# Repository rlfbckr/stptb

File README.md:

# Skills To Pay The Bills!
Online Workshop Series WS2020/21 HfK Bremen

Workshops:

- **2020-11-28** / **10:00** - **18:00** : [Designing Parts for *Machines and Installations* with OpenSCAD](openscad)
- **2020-12-21** / **10:00** - **18:00** : [Designing PCBs with Eagle](eagle)

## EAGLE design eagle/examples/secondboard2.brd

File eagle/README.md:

# Designing PCBs with Eagle

One day introduction into the PCB [(Printed Circuit Board)](https://en.wikipedia.org/wiki/Printed_circuit_board) CAD software **Eagle**  ([www.autodesk.com/products/eagle/overview](hthttps://www.autodesk.com/products/eagle/overview)). The workshop offers a fundamental introduction into concepts, user interface and workflow. A full workflow cycle - form schematic to board layout and the final production in a factory in china - will be explained.

- **Date:** Monday **2020-12-21** / **10:00** - **18:00**
- **Registration:** Send me an email or direct message for a **binding** registration. Please make sure that you are able to join the workshop for the **full day**. (The workshop is limited to **15 participants**)
- The workshop will be held **online via MS Teams.**

## Pre/Requirements:

1. Participants should have **GOOD/SOLID** knowledge in electronics and fundamental electric laws incl. reading schematics, soldering and some experiance with sourcing parts. (At leased you should have already made **some** circuits on breadboards or with perfboard ).
2. It could be helpful to have already a **little** project in mind.
3. Please install the free/educational version of  **EAGLE** form from the [autodesk website](https://www.autodesk.de/products/eagle/free-download?plc=F360&term=1-YEAR&support=ADVANCED&quantity=1). (It's now strangly bundeled with Fursion 360. Look for educational licence )
5. A **three button** mouse incl. **wheel** is **very** helpful!
4. Coffee and food by hand.

## Schedule x Content *(preliminary)*:

* **10:00 - 12:00** | *Fundamentals*

  1. Introduction
     - Why design your own PCBs?
     - Environmental Footprint?
     - *Design*ing PCB as a *designer*?
     - DIP vs SMD?
     - Materials
     - Fabrication in China or at home?
 
  2. Schematics
     - Eagle User Interface and basic concepts.
     - Adding Parts - **KNOW YOU PARTS!!!!!!!!!**
     - Libraries of Parts
     - Connecting Parts
     
  3. Q&A Time I
     - The participants can repeat and experiment the learned and ask questions  
     - Share your screen!

* **12:00 - 13:00** | *Lunch Break*

* **13:00 - 15:00** |  *Layouting a Board*

  4. Placing parts
  5. Ground plate
  6. Routing signals
  7. Vias
  8. Q&A Time II

* **15:00 - 16:00** | *Kaffee x Kuchen Break / BYOC (Bring your own Cake)*

* **16:00 - 18:00** | *Preparing for Production*

  9. Testing and Checking ERC + DRC
  10. Exporting Gerber Files
  11. Uploading files to your chinese manufacturer of choice!

* **18:00** | *EOW*

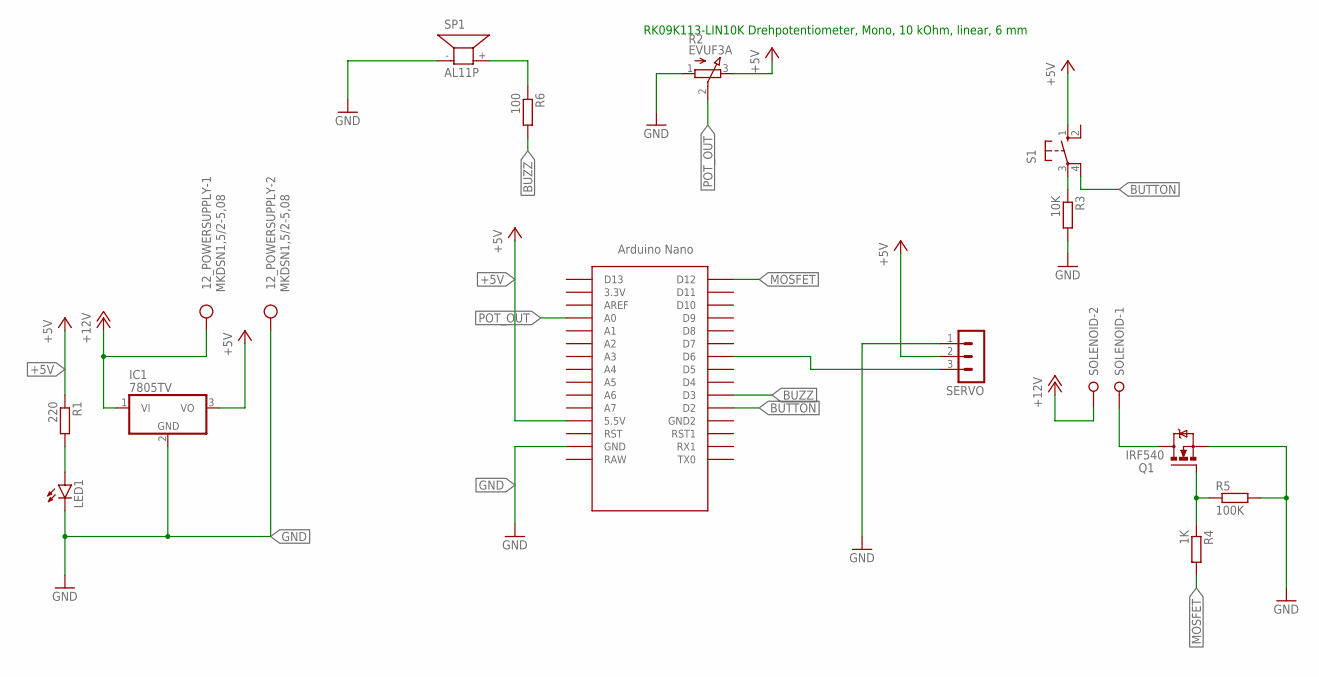
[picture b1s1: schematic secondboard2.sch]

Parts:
12_POWERSUPPLY: MKDSN1,5/2-5,08
IC1: 7805TV; TO220V
LED1: LED3MM
Q1: IRF540; TO220BV
R1: 220; R0805
R2: EVUF3A; EVUF
R3: 10K; R0805
R4: 1K; R0805
R5: 100K; R0805
R6: 100; R0805
S1: 10-XX; B3F-10XX
SERVO: MA03-1
SOLENOID: W237-02P; W237-132
SP1: AL11P
U$1: NANO

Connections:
+5V: IC1.3 (VO), R1.1, R2.3 (E), S1.1 (S), SERVO.2, U$1.5V (5.5V)
+12V: 12_POWERSUPPLY.1, IC1.1 (VI), SOLENOID.2
BUTTON: S1.4 (P1), U$1.D2
BUZZ: R6.2, U$1.D3
CONNECT: LED1.A, R1.2
GND: 12_POWERSUPPLY.2, IC1.2 (GND), LED1.K (C), Q1.S, R2.1 (A), R3.2, R5.2, SERVO.1, SP1.- (1), U$1.GND
MOSFET: R4.2, U$1.D12
unnamed: R3.1, S1.3
unnamed: R6.1, SP1.+ (2)
unnamed: Q1.D, SOLENOID.1
unnamed: SERVO.3, U$1.D6
unnamed: Q1.G, R4.1, R5.1
POT_OUT: R2.2 (S), U$1.A0

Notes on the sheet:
RK09K113-LIN10K Drehpotentiometer, Mono, 10 kOhm, linear, 6 mm

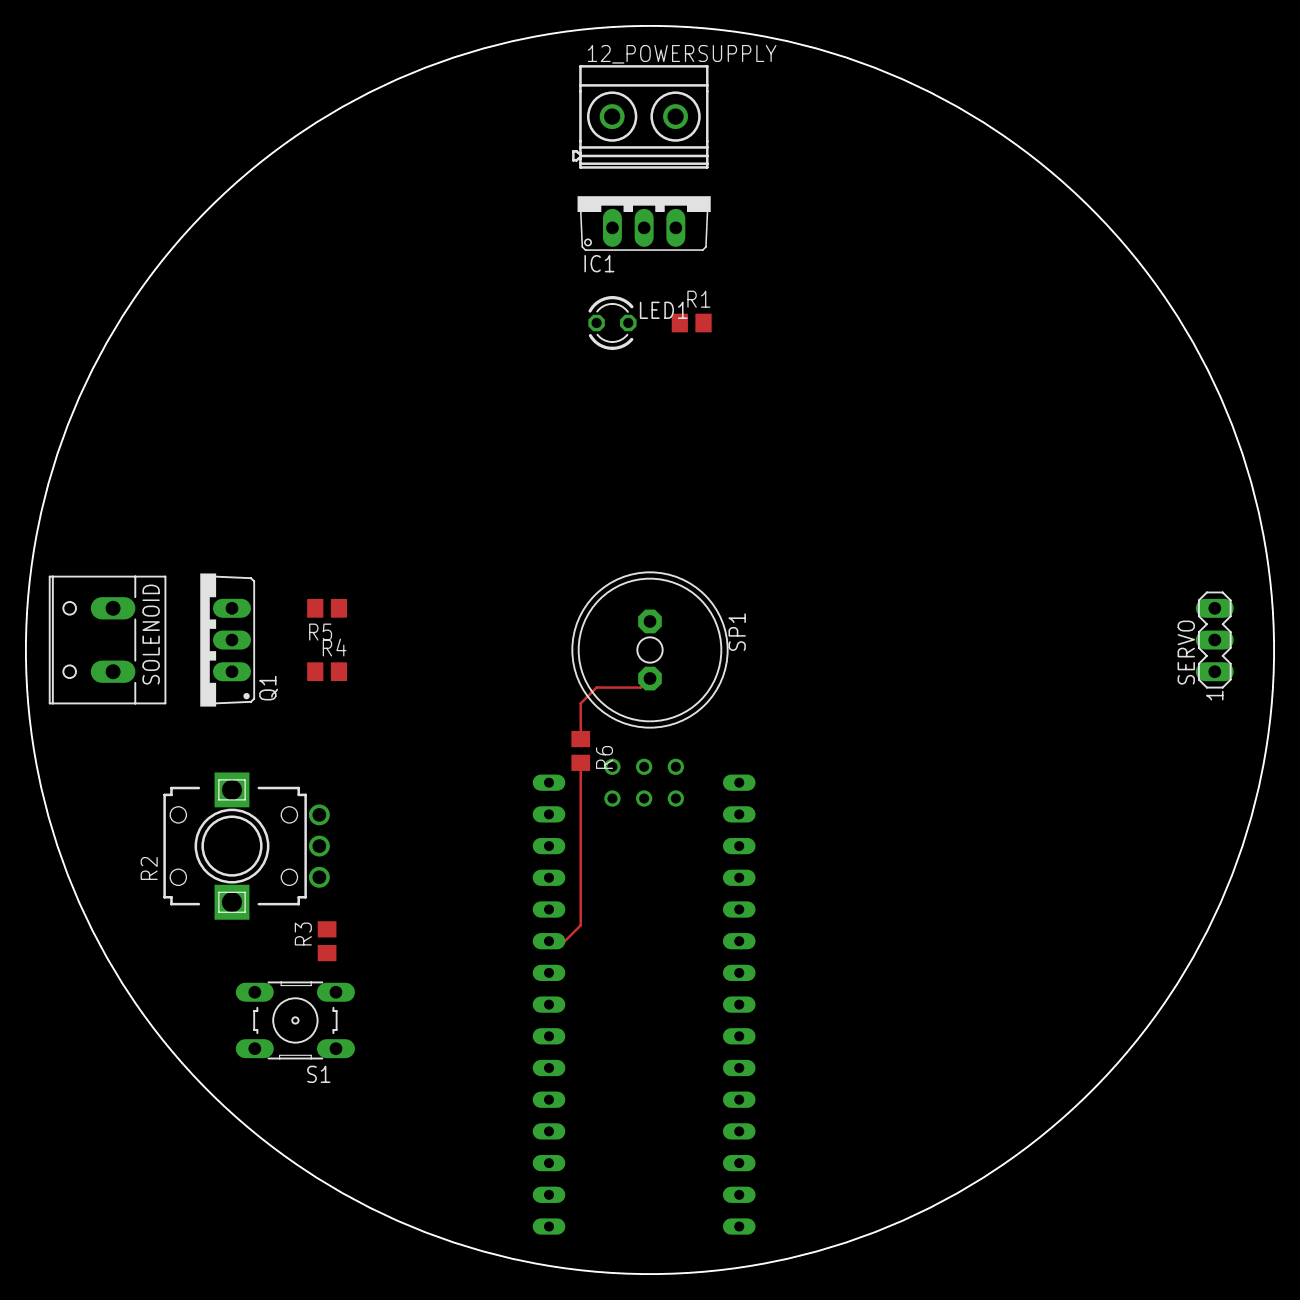
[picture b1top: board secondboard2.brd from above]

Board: 2 copper layers, 100.0 x 100.0 mm, 15 parts (0 on the bottom side), 13 nets.

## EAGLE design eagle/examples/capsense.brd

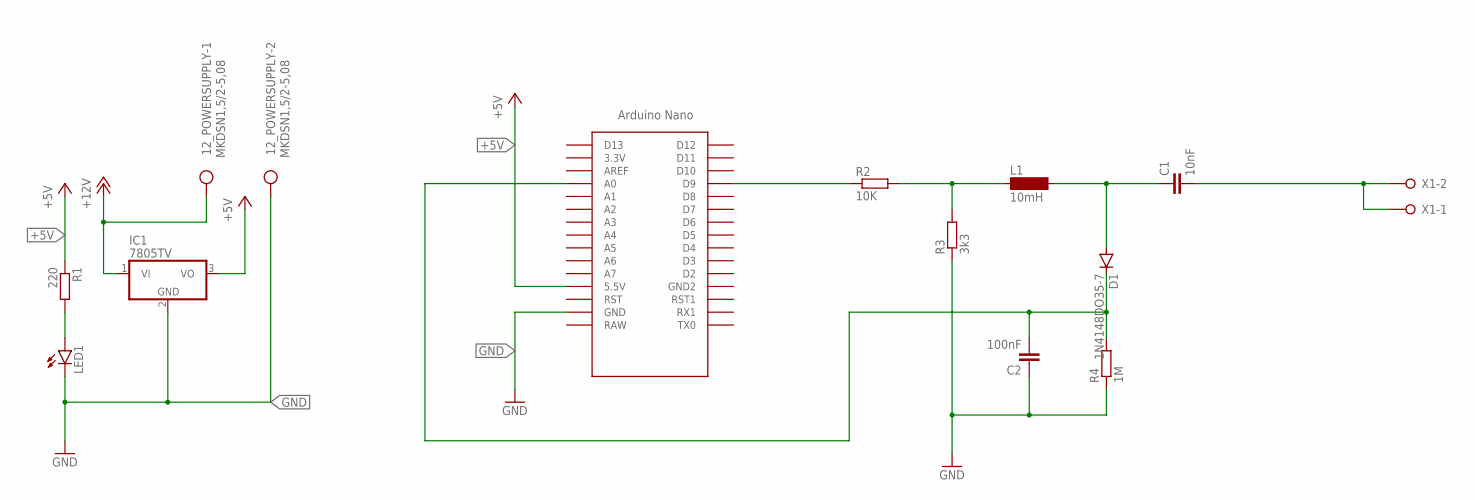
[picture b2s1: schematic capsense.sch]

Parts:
12_POWERSUPPLY: MKDSN1,5/2-5,08
C1: 10nF; C050-024X044
C2: 100nF; C050-024X044
D1: 1N4148DO35-7; DO35-7
IC1: 7805TV; TO220V
L1: 10mH; BS11
LED1: LED3MM
R1: 220; R0805
R2: 10K; 0207/7
R3: 3k3; 0207/7
R4: 1M; 0207/7
U$1: NANO
X1: W237-02P; W237-132

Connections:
+5V: IC1.3 (VO), R1.1, U$1.5V (5.5V)
+12V: 12_POWERSUPPLY.1, IC1.1 (VI)
CONNECT: LED1.A, R1.2
GND: 12_POWERSUPPLY.2, C2.1, IC1.2 (GND), LED1.K (C), R3.1, R4.1, U$1.GND
unnamed: R2.1, U$1.D9
unnamed: L1.1, R2.2, R3.2
unnamed: C1.1, D1.A, L1.2
unnamed: C1.2, X1.1, X1.2
unnamed: C2.2, D1.C, R4.2, U$1.A0

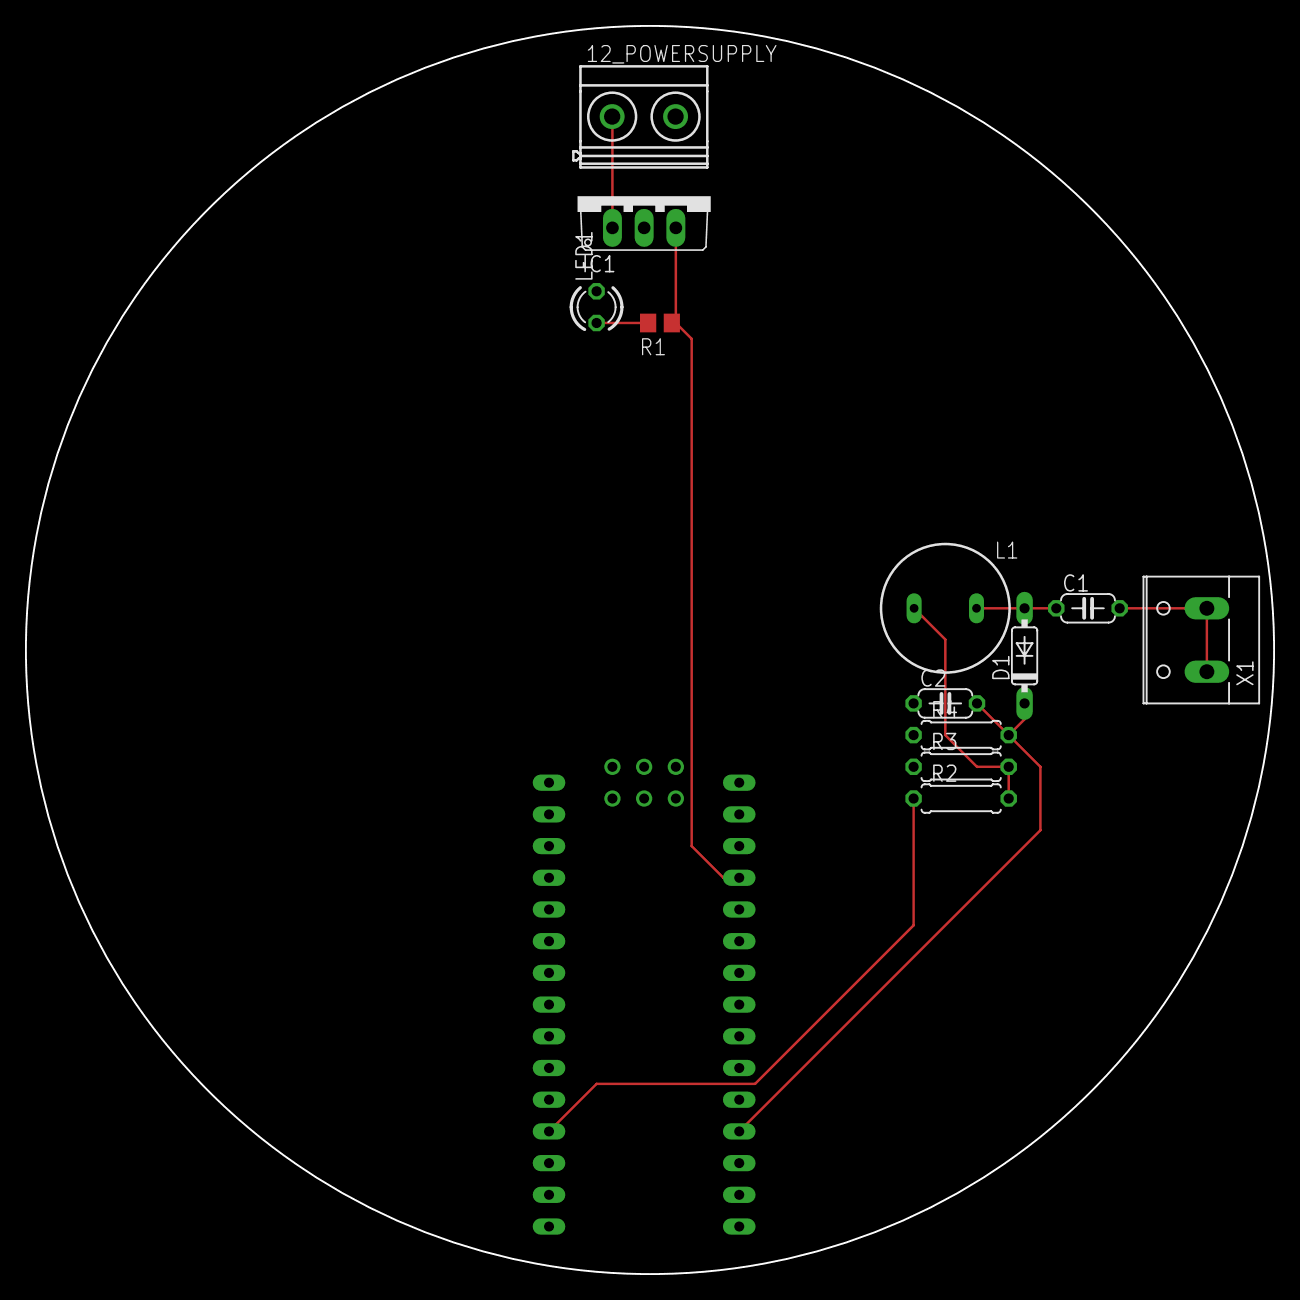
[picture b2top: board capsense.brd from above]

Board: 2 copper layers, 100.0 x 100.0 mm, 13 parts (0 on the bottom side), 9 nets.

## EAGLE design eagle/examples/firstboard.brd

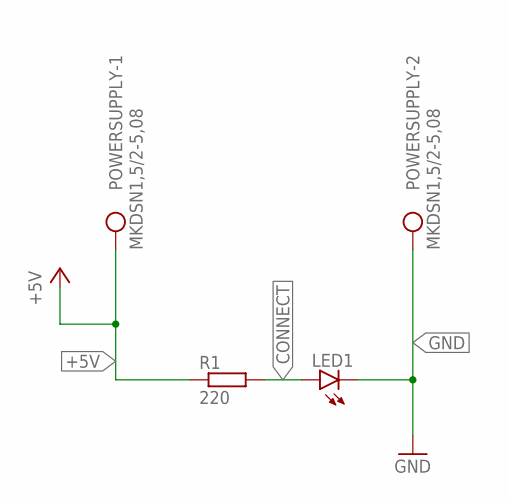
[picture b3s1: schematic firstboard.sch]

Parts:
LED1: LED3MM
POWERSUPPLY: MKDSN1,5/2-5,08
R1: 220; R0805

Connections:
+5V: POWERSUPPLY.1, R1.1
CONNECT: LED1.A, R1.2
GND: LED1.K (C), POWERSUPPLY.2

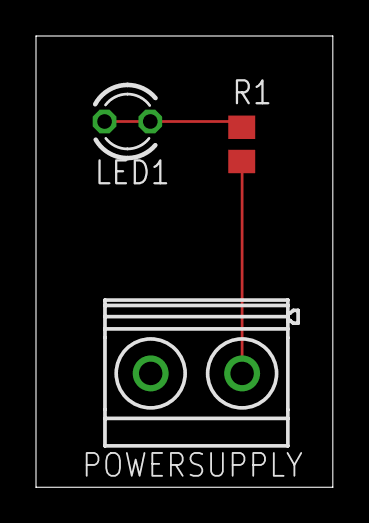
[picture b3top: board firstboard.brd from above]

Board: 2 copper layers, 16.5 x 25.1 mm, 3 parts (0 on the bottom side), 3 nets.

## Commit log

2020-11-14 init
2020-11-14 openscad..
2020-11-14 openscad workshop
2020-11-14 eagle workshop
2020-11-15 push
2020-11-15 swiss cheeese
2020-11-15 openscad
2020-11-23 star
2020-11-23 print
2020-11-24 enclosure
2020-11-24 cleaning
2020-11-27 mini
2020-11-27 text
2020-11-28 servo
2020-12-03 date
2020-12-03 link
2020-12-03 parts
2020-12-21 libs
2020-12-21 first example
2020-12-21 examples
